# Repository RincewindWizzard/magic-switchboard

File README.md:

# Magic Switchboard

A magic schwitchboard is a little box with four switches and four lamps colored in red, green, blue and yellow.
The switches have got hats in the same colors. You can change the position of the lamps and the hats in any way you want.
But the red switch always lights the red lamp, the blue the blue, the yellow the yellow and the green the green one.
How does this work?
The magician is the one operating the switchbox. He has to remember which switch was turned off last. 
He then hands off the box to the audience and asks them to rearrange the colors.
When the audience returns his box he remembers the sequence in which the lights turn on and turns the switches with matching color.
For the audience it seems like the colors are connected somehow.

[Youtube Video](https://youtu.be/IKBSlG797YQ)

# Wiring

You can find wiring instructions in the [Schematics](magic-switchboard.svg).
The [Attiny4313A](http://ww1.microchip.com/downloads/en/DeviceDoc/doc8246.pdf) can be powered with up to 5V.

With the [BC547](https://www.sparkfun.com/datasheets/Components/BC546.pdf) transistor you can safely drive a current up to 100 mA and voltage of 50V for your light bulbs. For bigger loads consider using [TIP100](https://www.onsemi.com/pub/Collateral/TIP100-D.PDF).

The voltage source for the arduino nano can be seperate to the voltage source of the lights, but they have to have a common ground (GND) for the circuit to work. For driving 230VAC (common household plug) light bulbs you might want to use a galvanic separation (opto-isolator). If you don't know what that means, don't try it.

If all lamps are off, the ATtiny is switched into sleep mode, which draws significant less current.
This circuit doesn't have a low power warning, so if there is strange behaviour (lamps dont turn on as expected) you might try change your batteries.

# How it Works
The sequence in which the lamps turn on is determined by last lever turned off.
After a longer sleep time (ca. 2.5sec) it resets to default = 0 lever.

| Lever (left to right) | Turn on Sequence |
| --------------------- |:----------------:|
| 0                     | 0, 1, 2, 3       |
| 1                     | 1, 0, 2, 3       |
| 2                     | 2, 3, 1, 0       |
| 3                     | 3, 2, 1, 0       |

In order to connect the correct colors from levers to lamps, you need to remember which lamp turns on next and flip the lever with the corresponding color.

You find the code [here](arduino/switchboard.ino).

# Parts List
- ON/OFF switch (MTS-102)
- color caps
- light bulb socket E10 with print pins
- LED light bulbs E10 in red, green, blue, yellow
- attiny4313A DIP-20
- 4x 10kOhms resistors
- 4x BC547 transistors TO-92
- capacitor 100uF
- Battery Clip for CR2477: https://www.digikey.de/product-detail/de/keystone-electronics/3039/36-3039-ND/3884009

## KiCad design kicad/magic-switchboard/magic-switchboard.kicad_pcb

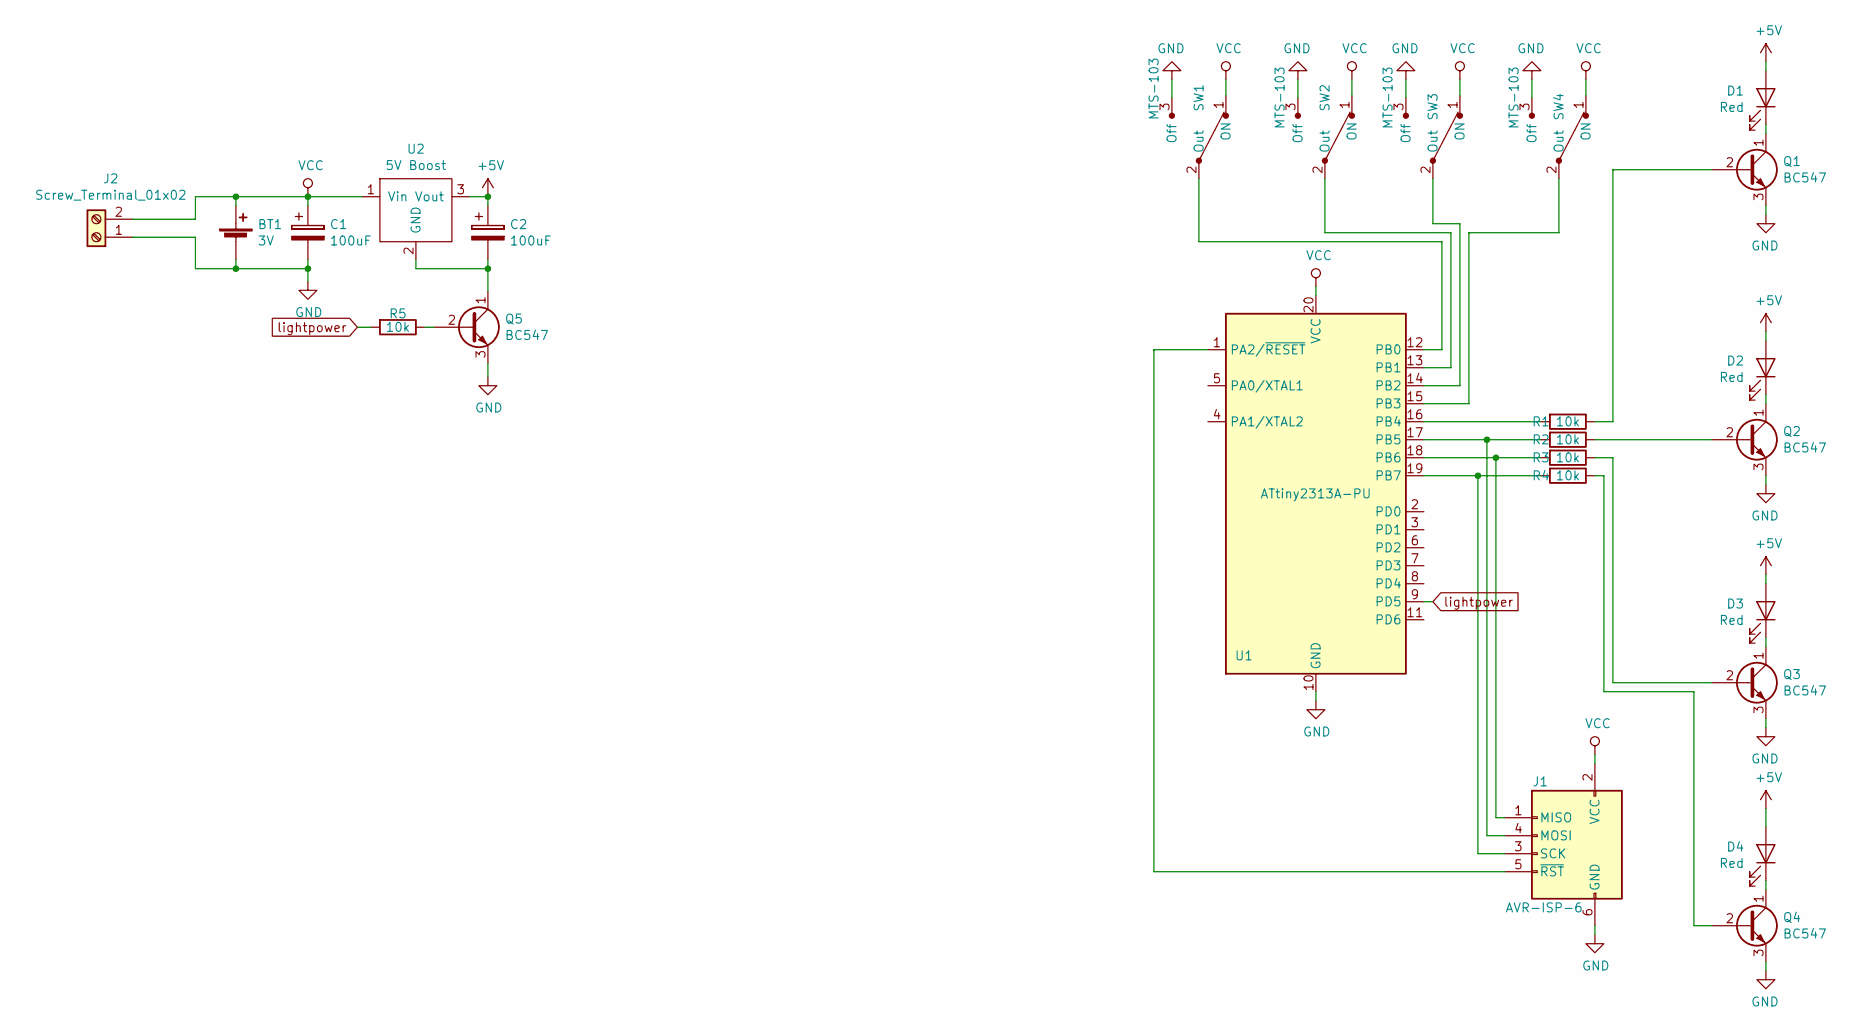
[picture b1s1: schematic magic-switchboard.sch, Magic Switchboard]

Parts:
BT1: 3V; BatteryHolder_Keystone_3009_1x2450
C1, C2: 100uF; CP_Radial_D6.3mm_P2.50mm
D1, D2, D3, D4: Red; E10 Edison Socket Print Pins
J1: AVR-ISP-6; ISP6
J2: Screw_Terminal_01x02; ScrewTerminal1x2
Q1, Q2, Q3, Q4, Q5: BC547; TO-92_Inline
R1, R2, R3, R4, R5: 10k; Resistor
SW1, SW2, SW3, SW4: MTS-103; MTS-103 Switch
U1: ATtiny2313A-PU; ATtiny2313
U2: 5V Boost; BoostConverter3Pin

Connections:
+5V: C2.1, D1.2 (A), D2.2 (A), D3.2 (A), D4.2 (A), U2.3 (Vout)
GND: BT1.2 (-), C1.2, J1.6 (GND), J2.1, Q1.3 (E), Q2.3 (E), Q3.3 (E), Q4.3 (E), Q5.3 (E), SW1.3 (Off), SW2.3 (Off), SW3.3 (Off), SW4.3 (Off), U1.10 (GND)
unnamed: C2.2, Q5.1 (C), U2.2 (GND)
unnamed: D1.1 (K), Q1.1 (C)
unnamed: D2.1 (K), Q2.1 (C)
unnamed: D3.1 (K), Q3.1 (C)
unnamed: D4.1 (K), Q4.1 (C)
unnamed: J1.1 (MISO), R3.2, U1.18 (PB6)
unnamed: J1.3 (SCK), R4.2, U1.19 (PB7)
unnamed: J1.4 (MOSI), R2.2, U1.17 (PB5)
unnamed: J1.5 (~RST), U1.1 (PA2/~RESET)
unnamed: Q1.2 (B), R1.1
unnamed: Q2.2 (B), R2.1
unnamed: Q3.2 (B), R3.1
unnamed: Q4.2 (B), R4.1
unnamed: Q5.2 (B), R5.1
unnamed: R1.2, U1.16 (PB4)
unnamed: SW1.2 (Out), U1.12 (PB0)
unnamed: SW2.2 (Out), U1.13 (PB1)
unnamed: SW3.2 (Out), U1.14 (PB2)
unnamed: SW4.2 (Out), U1.15 (PB3)
VCC: BT1.1 (+), C1.1, J1.2 (VCC), J2.2, SW1.1 (ON), SW2.1 (ON), SW3.1 (ON), SW4.1 (ON), U1.20 (VCC), U2.1 (Vin)
lightpower: R5.2, U1.9 (PD5)

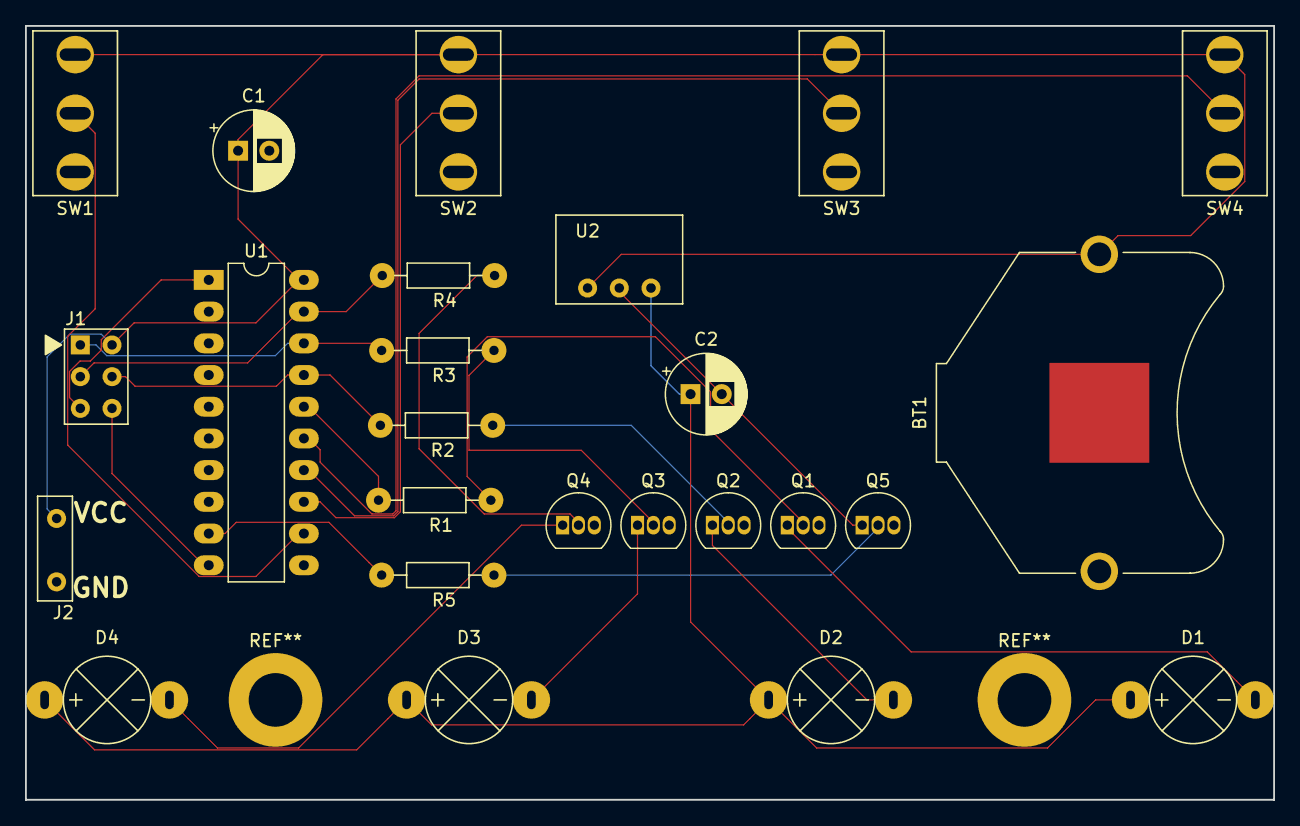
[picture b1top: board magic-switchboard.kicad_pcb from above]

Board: 2 copper layers, 100.0 x 62.0 mm, 25 parts (0 on the bottom side), 23 nets.

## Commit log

2016-04-29 initial
2016-04-29 komplizierte reihenfolgen
2016-04-29 Dokumentation geschrieben
2017-06-24 works now for atmega328p mcu
2017-08-02 Added GPL
2018-10-23 Added documentation
2018-10-23 Added PNG Schematics
2019-01-08 pcb layout
2019-01-22 unfertige mosfet schaltung
2019-01-24 p-channel deadman trap
2019-01-26 redone pcb v3
2019-01-27 created gerbers for v3
2019-01-27 attiny2313 board
2019-02-23 rewritten arduino code
2019-02-23 aufgeräumt für v4 (attiny4313)
2019-03-30 Zwischenboden Bohrplan
2019-03-30 Readme updata
2024-03-30 Schematic in der Doku angepasst
2025-04-11 COde gerettet
2025-04-11 ein paar bilder
